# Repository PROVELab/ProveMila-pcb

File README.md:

View this project on [CADLAB.io](https://cadlab.io/project/27803). 

# ProveMila-pcb
Repository for KiCad files. Access through cadlab.io to view schematic and PCB

## Contents
* describe the different projects and files in this repo

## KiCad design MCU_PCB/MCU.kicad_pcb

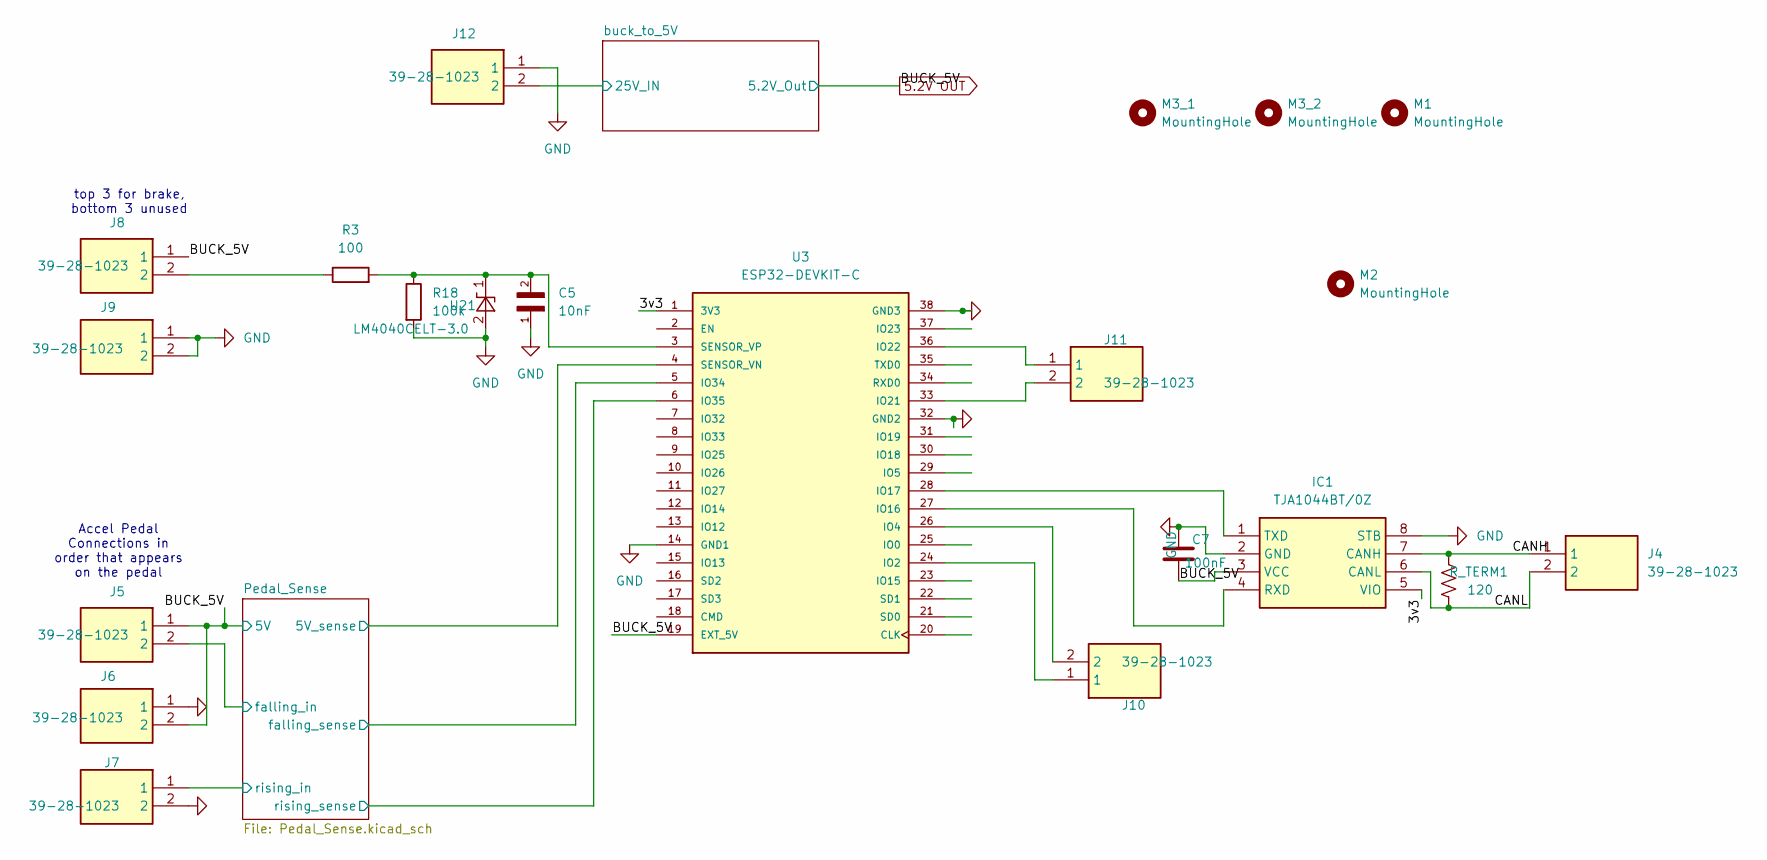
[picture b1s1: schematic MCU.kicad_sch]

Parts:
C5: 10nF; C_0805_2012Metric_Pad1.18x1.45mm_HandSolder
C7: 100nF; C_0805_2012Metric_Pad1.18x1.45mm_HandSolder; MPN 1206B104K500CT
IC1: TJA1044BT/0Z; SOIC127P600X175-8N; Mouser Part Number 771-TJA1044BT/0Z
J4, J5, J6, J7, J8, J9, J10, J11, J12: 39-28-1023; Mouser Part Number 538-39-28-1023
M1, M2, M3_1, M3_2: MountingHole; MountingHole_3.2mm_M3
R3: 100; R_0805_2012Metric_Pad1.20x1.40mm_HandSolder
R18: 100k; R_0805_2012Metric_Pad1.20x1.40mm_HandSolder
R_TERM1: 120; R_0805_2012Metric_Pad1.20x1.40mm_HandSolder; MPN RMCF1206JT120R
U3: ESP32-DEVKIT-C; MODULE_ESP32-DEVKITC; PARTREV N/A
U21: LM4040CELT-3.0; SOT-23

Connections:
5.2V OUT: C7.1, IC1.3 (VCC), J5.1, J6.2, J8.1, U3.19 (EXT_5V); also elsewhere on the board
/3v3: IC1.5 (VIO), U3.1 (3V3)
/CANH: IC1.7 (CANH), J4.1, R_TERM1.1
/CANL: IC1.6 (CANL), J4.2, R_TERM1.2
/Pedal_Sense/5V_sense: U3.4 (SENSOR_VN); also elsewhere on the board
/Pedal_Sense/falling_in: J5.2; also elsewhere on the board
/Pedal_Sense/falling_sense: U3.5 (IO34); also elsewhere on the board
/Pedal_Sense/rising_in: J7.1; also elsewhere on the board
/Pedal_Sense/rising_sense: U3.6 (IO35); also elsewhere on the board
/buck_to_5V/25V_IN: J12.2; also elsewhere on the board
GND: C5.1, C7.2, IC1.2 (GND), IC1.8 (STB), J6.1, J7.2, J9.1, J9.2, J12.1, R18.2, U3.14 (GND1), U3.32 (GND2), U3.38 (GND3), U21.2 (A); also elsewhere on the board
unnamed: IC1.4 (RXD), U3.27 (IO16)
unnamed: IC1.1 (TXD), U3.28 (IO17)
unnamed: J8.2, R3.1
unnamed: J10.1, U3.24 (IO2)
unnamed: J10.2, U3.26 (IO4)
unnamed: J11.2, U3.33 (IO21)
unnamed: J11.1, U3.36 (IO22)
unnamed: C5.2, R3.2, R18.1, U3.3 (SENSOR_VP), U21.1 (K)

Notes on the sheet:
Accel Pedal Connections in order that appears on the pedal
top 3 for brake, bottom 3 unused

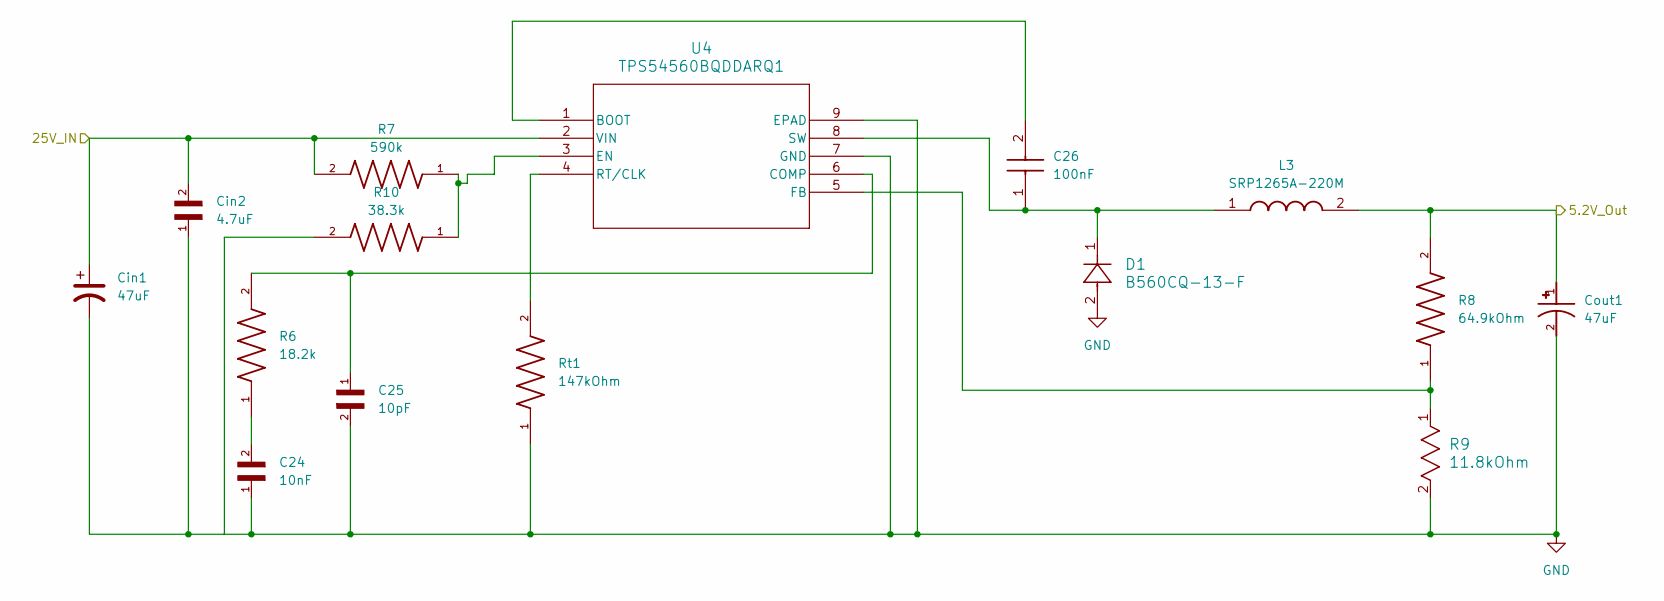
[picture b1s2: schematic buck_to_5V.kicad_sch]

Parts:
C24: 10nF; C_0805_2012Metric_Pad1.18x1.45mm_HandSolder
C25: 10pF; C_0805_2012Metric_Pad1.18x1.45mm_HandSolder
C26: 100nF; C_0805_2012Metric_Pad1.18x1.45mm_HandSolder
Cin1: 47uF; CP_Elec_6.3x7.7
Cin2: 4.7uF; C_1210_3225Metric_Pad1.33x2.70mm_HandSolder
Cout1: 47uF; CP_EIA-3528-21_Kemet-B_HandSolder
D1: B560CQ-13-F; D_SMC
L3: SRP1265A-220M; SRP1265A; Mouser Part Number 652-SRP1265A-220M
R6: 18.2k; R_0805_2012Metric_Pad1.20x1.40mm_HandSolder
R7: 590k; R_0805_2012Metric_Pad1.20x1.40mm_HandSolder
R8: 64.9kOhm; R_0805_2012Metric_Pad1.20x1.40mm_HandSolder
R9: 11.8kOhm; R_0805_2012Metric_Pad1.20x1.40mm_HandSolder
R10: 38.3k; R_0805_2012Metric_Pad1.20x1.40mm_HandSolder
Rt1: 147kOhm; R_0805_2012Metric_Pad1.20x1.40mm_HandSolder
U4: TPS54560BQDDARQ1; SOIC-8-1EP_3.9x4.9mm_P1.27mm_EP2.29x3mm

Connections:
5.2V OUT: Cout1.1, L3.2, R8.2; also elsewhere on the board
/buck_to_5V/25V_IN: Cin1.1, Cin2.2, R7.2, U4.2 (VIN); also elsewhere on the board
GND: C24.1, C25.2, Cin1.2, Cin2.1, Cout1.2, D1.2, R9.2, R10.2, Rt1.1, U4.7 (GND), U4.9 (EPAD); also elsewhere on the board
unnamed: C24.2, R6.1
unnamed: C26.2, U4.1 (BOOT)
unnamed: C25.1, R6.2, U4.6 (COMP)
unnamed: R7.1, R10.1, U4.3 (EN)
unnamed: R8.1, R9.1, U4.5 (FB)
unnamed: Rt1.2, U4.4 (RT/CLK)
unnamed: C26.1, D1.1, L3.1, U4.8 (SW)

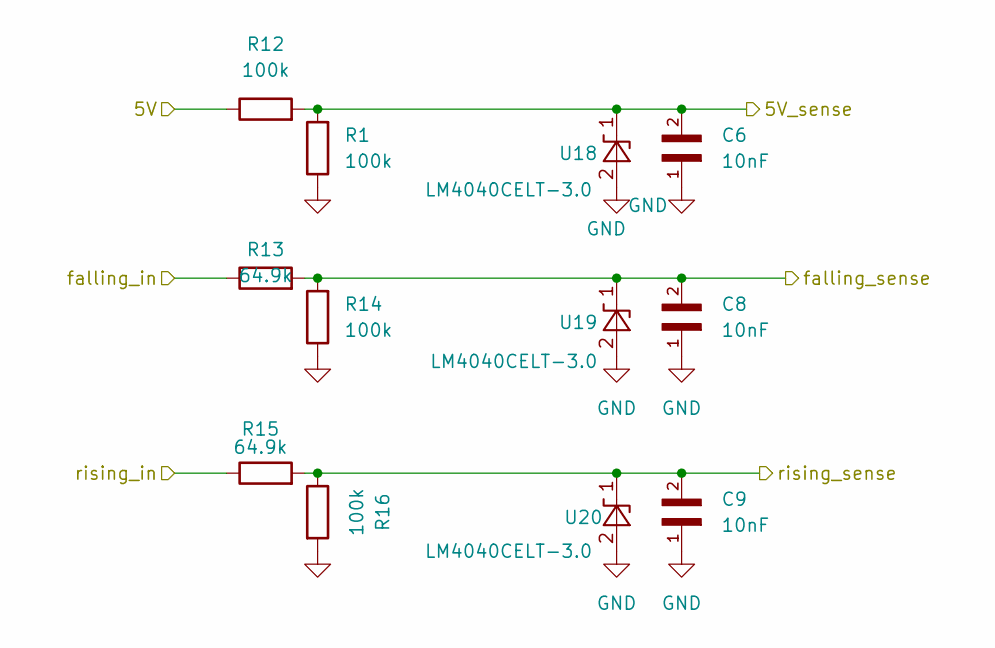
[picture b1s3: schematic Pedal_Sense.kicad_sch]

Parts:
C6, C8, C9: 10nF; C_0805_2012Metric_Pad1.18x1.45mm_HandSolder
R1, R12, R14, R16: 100k; R_0805_2012Metric_Pad1.20x1.40mm_HandSolder
R13, R15: 64.9k; R_0805_2012Metric_Pad1.20x1.40mm_HandSolder
U18, U19, U20: LM4040CELT-3.0; SOT-23

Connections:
5.2V OUT: R12.1; also elsewhere on the board
/Pedal_Sense/5V_sense: C6.2, R1.2, R12.2, U18.1 (K); also elsewhere on the board
/Pedal_Sense/falling_in: R13.1; also elsewhere on the board
/Pedal_Sense/falling_sense: C8.2, R13.2, R14.2, U19.1 (K); also elsewhere on the board
/Pedal_Sense/rising_in: R15.1; also elsewhere on the board
/Pedal_Sense/rising_sense: C9.2, R15.2, R16.1, U20.1 (K); also elsewhere on the board
GND: C6.1, C8.1, C9.1, R1.1, R14.1, R16.2, U18.2 (A), U19.2 (A), U20.2 (A); also elsewhere on the board

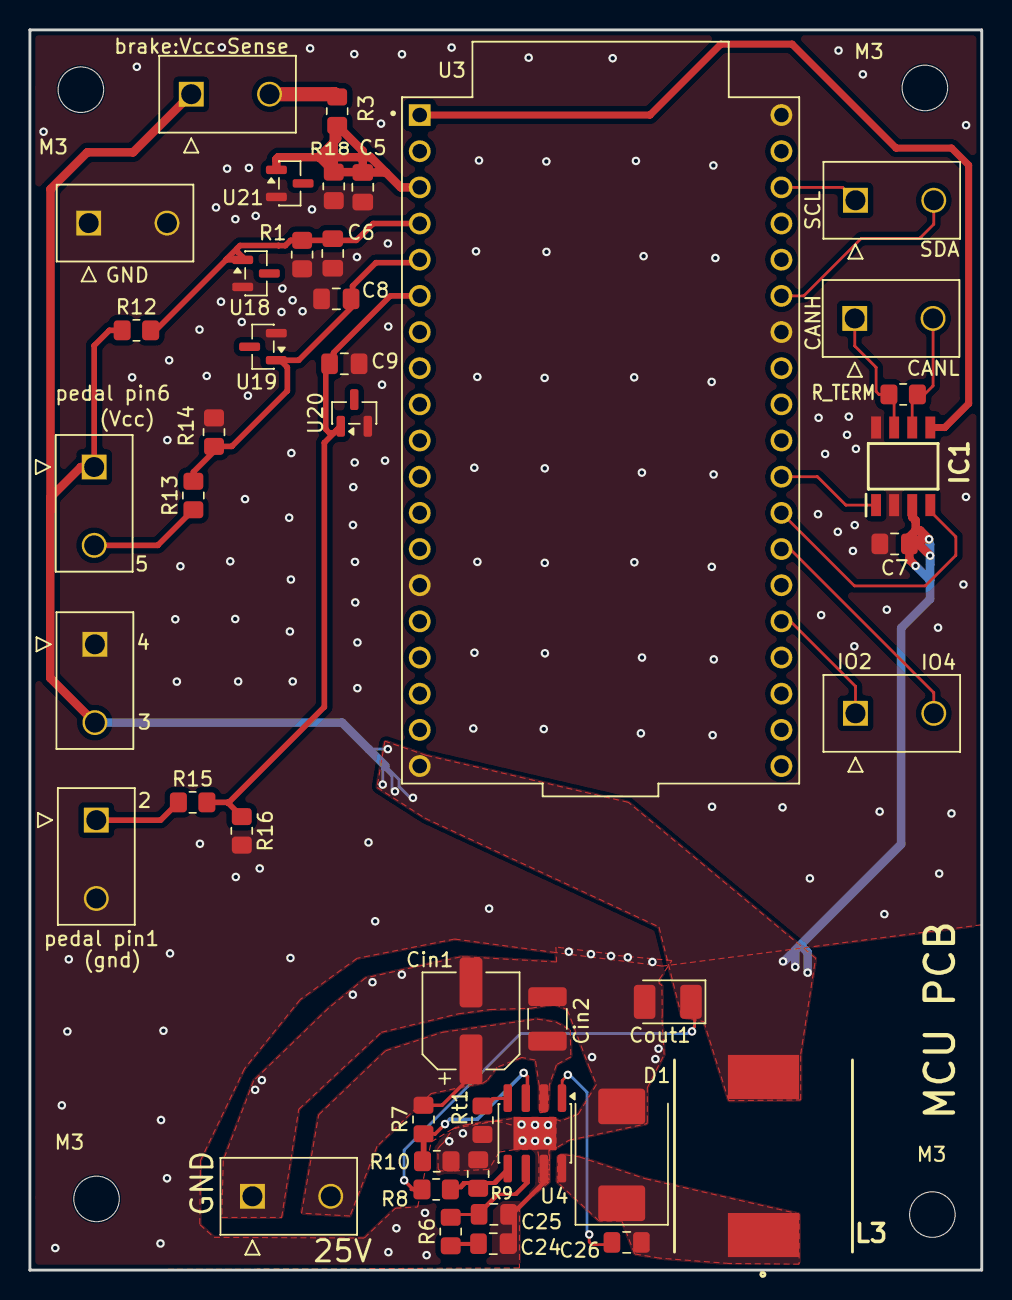
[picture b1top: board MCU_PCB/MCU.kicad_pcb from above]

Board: 2 copper layers, 66.8 x 87.1 mm, 48 parts (0 on the bottom side), 26 nets.

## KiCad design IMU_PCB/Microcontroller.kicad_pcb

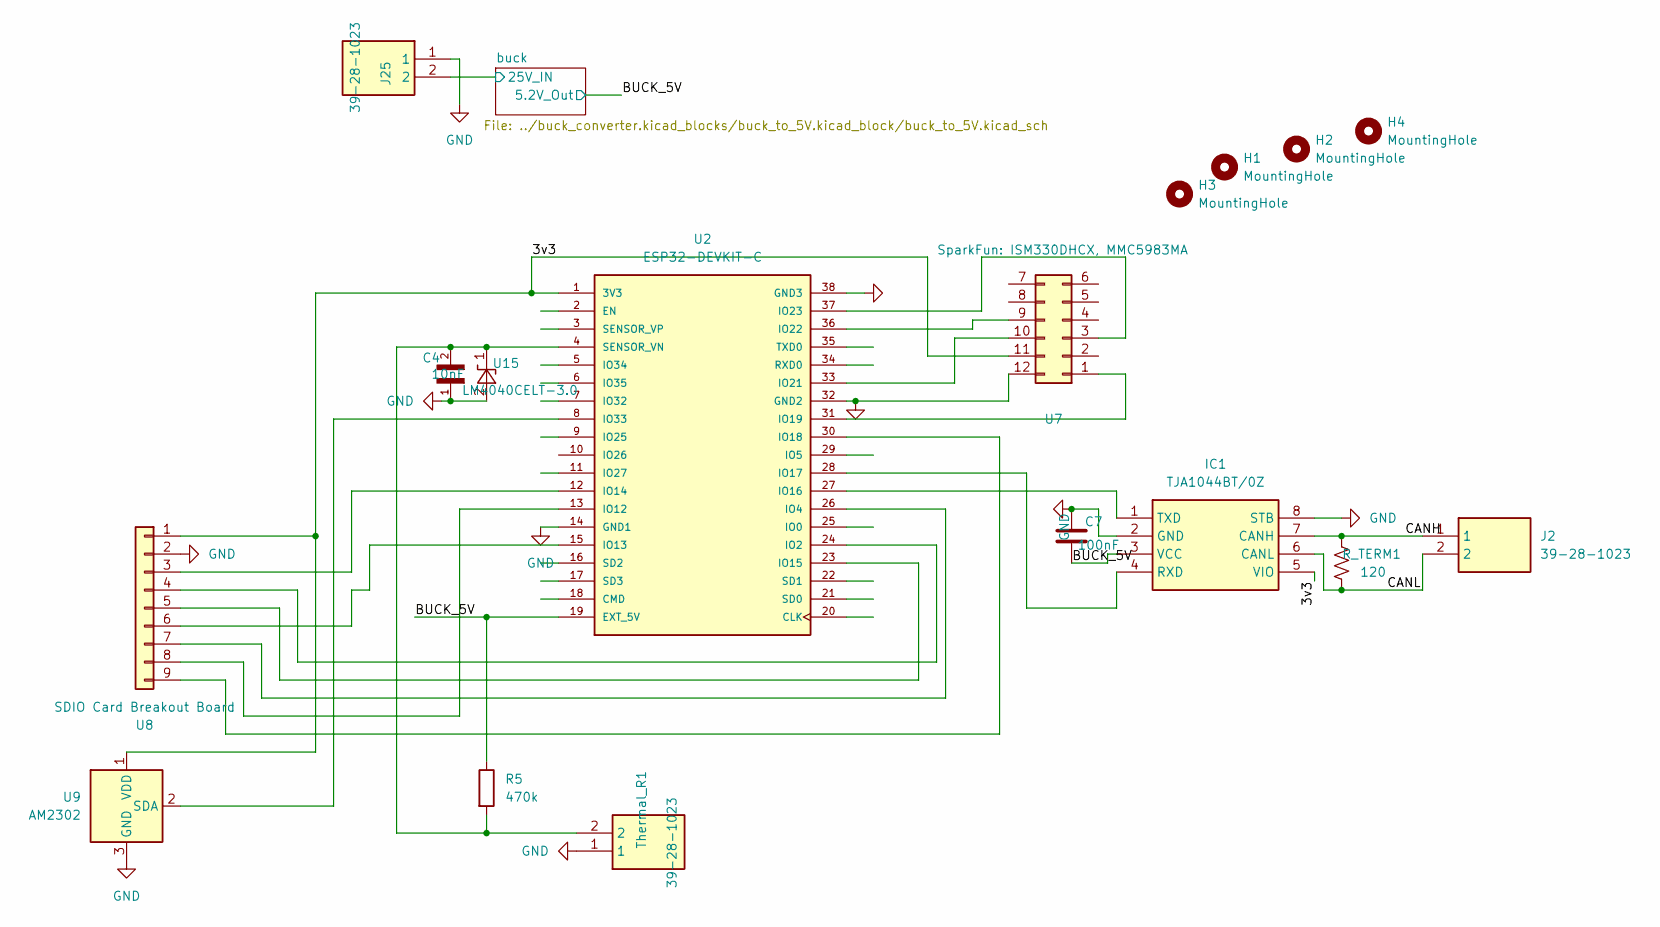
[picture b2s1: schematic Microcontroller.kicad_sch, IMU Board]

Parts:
C4: 10nF; C_0805_2012Metric_Pad1.18x1.45mm_HandSolder
C7: 100nF; C_0805_2012Metric_Pad1.18x1.45mm_HandSolder; MPN 1206B104K500CT
H1, H2, H3, H4: MountingHole; MountingHole_3.2mm_M3
IC1: TJA1044BT/0Z; SOIC127P600X175-8N; Mouser Part Number 771-TJA1044BT/0Z
J2, J25: 39-28-1023; Mouser Part Number 538-39-28-1023
R5: 470k; R_0805_2012Metric
R_TERM1: 120; R_0805_2012Metric_Pad1.20x1.40mm_HandSolder; MPN RMCF1206JT120R
Thermal_R1: 39-28-1023; Mouser Part Number 538-39-28-1023
U2: ESP32-DEVKIT-C; MODULE_ESP32-DEVKITC; PARTREV N/A
U7: SparkFun: ISM330DHCX, MMC5983MA; SparkFun 9DoF IMU Breakout - ISM330DHCX, MMC5983MA (Qwiic)
U8: SDIO Card Breakout Board; Adafruit SDIO card breakout
U9: AM2302; ASAIR_AM2302_P2.54mm_Vertical
U15: LM4040CELT-3.0; SOT-23

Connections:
/3v3: IC1.5 (VIO), U2.1 (3V3), U7.11, U8.1, U9.1 (VDD)
/BUCK_5V: C7.1, IC1.3 (VCC), R5.1, U2.19 (EXT_5V); also elsewhere on the board
/CANH: IC1.7 (CANH), J2.1, R_TERM1.1
/CANL: IC1.6 (CANL), J2.2, R_TERM1.2
/buck/25V_IN: J25.2; also elsewhere on the board
GND: C4.1, C7.2, IC1.2 (GND), IC1.8 (STB), J25.1, Thermal_R1.1, U2.14 (GND1), U2.32 (GND2), U2.38 (GND3), U7.12, U8.2, U9.3 (GND), U9.4 (GND), U15.2 (A); also elsewhere on the board
unnamed: IC1.4 (RXD), U2.28 (IO17)
unnamed: IC1.1 (TXD), U2.27 (IO16)
unnamed: U2.24 (IO2), U8.4
unnamed: U2.26 (IO4), U8.7
unnamed: U2.13 (IO12), U8.8
unnamed: U2.15 (IO13), U8.6
unnamed: U2.12 (IO14), U8.3
unnamed: U2.23 (IO15), U8.5
unnamed: U2.30 (IO18), U8.9
unnamed: U2.31 (IO19), U7.1
unnamed: U2.33 (IO21), U7.10
unnamed: U2.36 (IO22), U7.9
unnamed: U2.37 (IO23), U7.3
unnamed: U2.8 (IO33), U9.2 (SDA)
unnamed: C4.2, R5.2, Thermal_R1.2, U2.4 (SENSOR_VN), U15.1 (K)

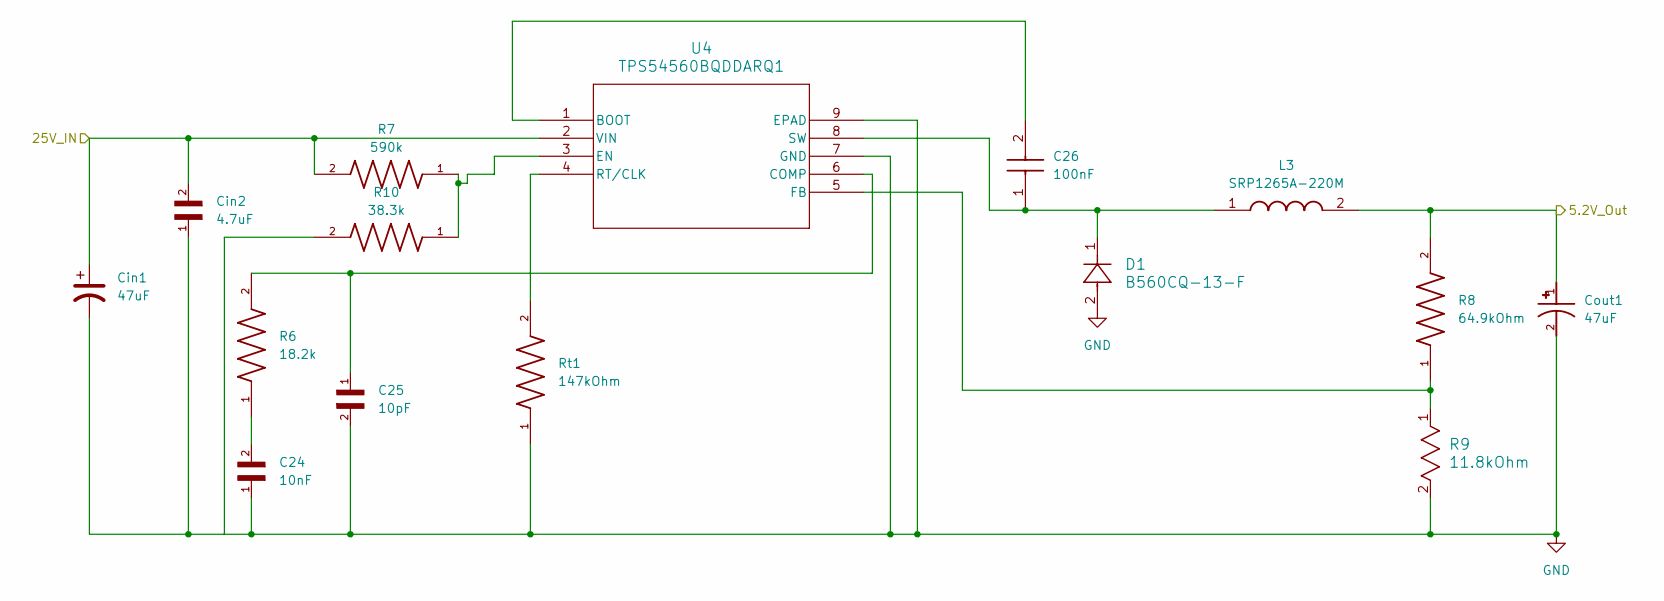
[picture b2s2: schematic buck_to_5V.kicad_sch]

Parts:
C24: 10nF; C_0805_2012Metric_Pad1.18x1.45mm_HandSolder
C25: 10pF; C_0805_2012Metric_Pad1.18x1.45mm_HandSolder
C26: 100nF; C_0805_2012Metric_Pad1.18x1.45mm_HandSolder
Cin1: 47uF; CP_Elec_6.3x7.7
Cin2: 4.7uF; C_1210_3225Metric_Pad1.33x2.70mm_HandSolder
Cout1: 47uF; CP_EIA-3528-21_Kemet-B_HandSolder
D1: B560CQ-13-F; D_SMC
L3: SRP1265A-220M; SRP1265A; Mouser Part Number 652-SRP1265A-220M
R6: 18.2k; R_0805_2012Metric_Pad1.20x1.40mm_HandSolder
R7: 590k; R_0805_2012Metric_Pad1.20x1.40mm_HandSolder
R8: 64.9kOhm; R_0805_2012Metric_Pad1.20x1.40mm_HandSolder
R9: 11.8kOhm; R_0805_2012Metric_Pad1.20x1.40mm_HandSolder
R10: 38.3k; R_0805_2012Metric_Pad1.20x1.40mm_HandSolder
Rt1: 147kOhm; R_0805_2012Metric_Pad1.20x1.40mm_HandSolder
U4: TPS54560BQDDARQ1; SOIC-8-1EP_3.9x4.9mm_P1.27mm_EP2.29x3mm

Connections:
/BUCK_5V: Cout1.1, L3.2, R8.2; also elsewhere on the board
/buck/25V_IN: Cin1.1, Cin2.2, R7.2, U4.2 (VIN); also elsewhere on the board
GND: C24.1, C25.2, Cin1.2, Cin2.1, Cout1.2, D1.2, R9.2, R10.2, Rt1.1, U4.7 (GND), U4.9 (EPAD); also elsewhere on the board
unnamed: C24.2, R6.1
unnamed: C26.2, U4.1 (BOOT)
unnamed: C25.1, R6.2, U4.6 (COMP)
unnamed: R7.1, R10.1, U4.3 (EN)
unnamed: R8.1, R9.1, U4.5 (FB)
unnamed: Rt1.2, U4.4 (RT/CLK)
unnamed: C26.1, D1.1, L3.1, U4.8 (SW)

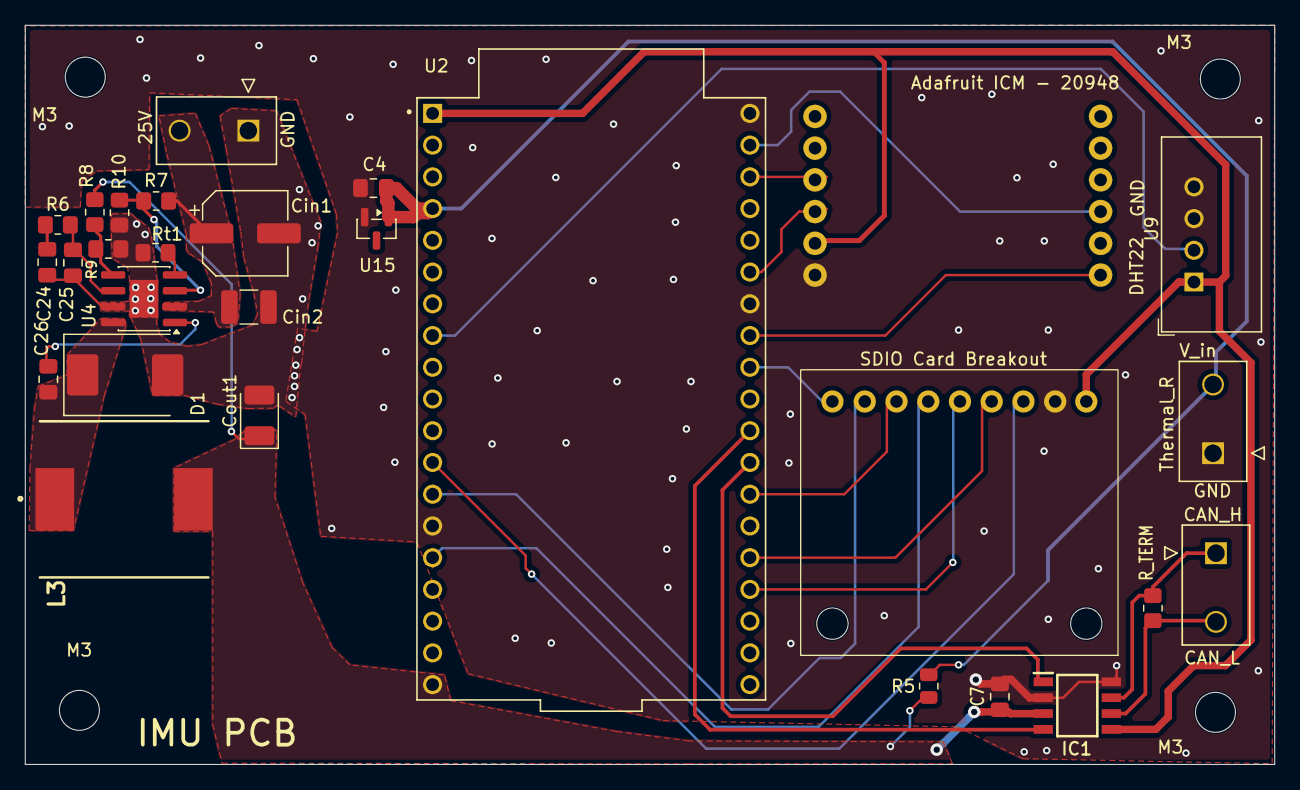
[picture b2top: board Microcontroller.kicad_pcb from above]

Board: 2 copper layers, 100.0 x 59.2 mm, 32 parts (1 on the bottom side), 28 nets.

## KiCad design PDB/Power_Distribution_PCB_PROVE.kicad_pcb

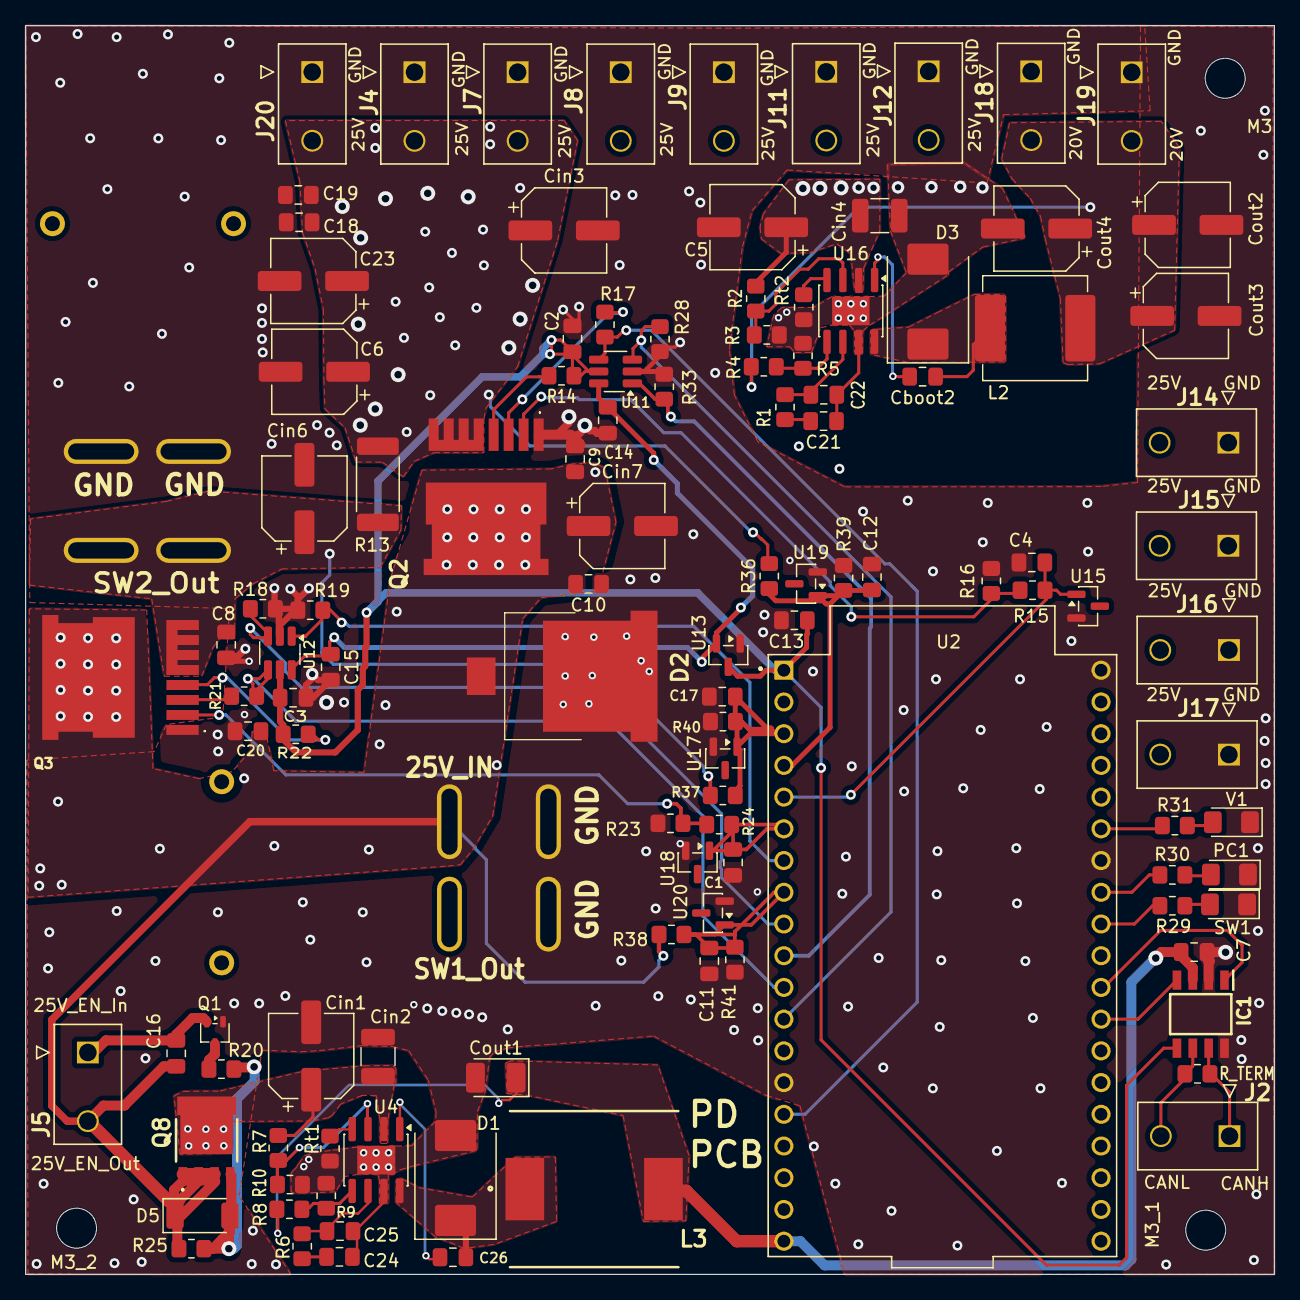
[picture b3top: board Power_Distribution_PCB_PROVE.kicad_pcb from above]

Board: 4 copper layers, 100.0 x 100.0 mm, 119 parts (0 on the bottom side), 53 nets.

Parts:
C1, C4, C11, C12, C17, C24: 10nF; C_0805_2012Metric_Pad1.18x1.45mm_HandSolder
C2, C3, C7, C8, C9, C10, C13, C14, C15, C16, C18, C19, C20, C26: 100nF; C_0805_2012Metric_Pad1.18x1.45mm_HandSolder
C5, C6, C23: 47uF; CP_Elec_6.3x7.7
C21: 3.9nF; C_0805_2012Metric_Pad1.18x1.45mm_HandSolder
C22: 330pF; C_0805_2012Metric_Pad1.18x1.45mm_HandSolder
C25: 10pF; C_0805_2012Metric_Pad1.18x1.45mm_HandSolder
Cboot2: 100nF; C_0805_2012Metric_Pad1.18x1.45mm_HandSolder
Cin1, Cin3, Cin6, Cin7: 47uF; CP_Elec_6.3x7.7
Cin2, Cin4: 4.7uF; C_1210_3225Metric_Pad1.33x2.70mm_HandSolder
Cout1: 47uF; CP_EIA-3528-21_Kemet-B_HandSolder
Cout2, Cout3, Cout4: 47uF; CP_Elec_6.3x7.7
D1, D3: B560CQ-13-F; D_SMC
D2: SLD8S30A
D5: PDZVTR10B; D_SOD-128
IC1: TJA1044BT/0Z; SOIC127P600X175-8N
J1, J3: Conn_02x02_Top_Bottom; Anderson_PP1545_45A_2b2
J2, J4, J5, J7, J8, J9, J11, J12, J14, J15, J16, J17, J18, J19, J20: 39-28-1023
L2: 8.2uH; L_Vishay_IHLP-3232
L3: SRP1265A-220M; SRP1265A
M3, M3_1, M3_2: MountingHole; MountingHole_3.2mm_M3
PC1: SML-S13UTT68; LED_1206_3216Metric_Pad1.42x1.75mm_HandSolder
Q1: DTC144EU3HZGT106; SOT-323_SC-70
Q2, Q3: BTH500151LUAAUMA1; BTS500101LUA
Q8: BUK6Y55-80PX
R1: 36.5k; R_0805_2012Metric_Pad1.20x1.40mm_HandSolder
R2, R7: 590k; R_0805_2012Metric_Pad1.20x1.40mm_HandSolder
R3, R10: 38.3k; R_0805_2012Metric_Pad1.20x1.40mm_HandSolder
R4: 271kOhm; R_0805_2012Metric_Pad1.20x1.40mm_HandSolder
R5: 11.3kOhm; R_0805_2012Metric_Pad1.20x1.40mm_HandSolder
R6, R18, R19, R20, R28, R33: 18.2k; R_0805_2012Metric_Pad1.20x1.40mm_HandSolder
R8: 64.9kOhm; R_0805_2012Metric_Pad1.20x1.40mm_HandSolder
R9: 11.8kOhm; R_0805_2012Metric_Pad1.20x1.40mm_HandSolder
R13: 470; R_2512_6332Metric_Pad1.40x3.35mm_HandSolder
R14, R15, R17, R21, R22, R24: 4.7k; R_0805_2012Metric_Pad1.20x1.40mm_HandSolder
R16, R23: 2k; R_0805_2012Metric_Pad1.20x1.40mm_HandSolder
R25, R39, R40, R41: 100k; R_0805_2012Metric_Pad1.20x1.40mm_HandSolder
R29, R30, R31: 270; R_0805_2012Metric_Pad1.20x1.40mm_HandSolder
R36, R37, R38: 1M; R_0805_2012Metric_Pad1.20x1.40mm_HandSolder
R_TERM1: 120; R_0805_2012Metric_Pad1.20x1.40mm_HandSolder
Rt1: 147kOhm; R_0805_2012Metric_Pad1.20x1.40mm_HandSolder
Rt2: 133kOhm; R_0805_2012Metric_Pad1.20x1.40mm_HandSolder
SW1: SML-S13UTT68; LED_1206_3216Metric_Pad1.42x1.75mm_HandSolder
U2: ESP32-DEVKIT-C; MODULE_ESP32-DEVKITC
U4, U16: TPS54560BQDDARQ1; SOIC-8-1EP_3.9x4.9mm_P1.27mm_EP2.29x3mm
U11, U12: 74LVC1G175; SOT-23-6_Handsoldering
U13: TLV809EA29DBZR; SOT-23
U15, U17, U18, U19, U20: LM4040CELT-3.0; SOT-23
V1: SML-S13UTT68; LED_1206_3216Metric_Pad1.42x1.75mm_HandSolder

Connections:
/3v3: C2.2, C3.2, C13.1, IC1.5 (VIO), R14.1, R22.1, U2.1 (3V3), U11.5 (VCC), U12.5 (VCC), U13.3 (V_{DD})
/25V_In: C9.2, C10.2, C16.1, C20.2, Cin7.1, D2.1 (K), D5.1 (K), J1.1, J5.2, Q2.9 (VS_1), Q2.10 (VS_2), Q2.11 (VS_3), Q3.9 (VS_1), Q3.10 (VS_2), Q3.11 (VS_3), Q8.1 (S_1), Q8.2 (S_2), Q8.3 (S_3), R25.1, R38.2
/BUCK_5V: C7.1, Cout1.1, IC1.3 (VCC), L3.2, R8.2, U2.19 (EXT_5V)
/CANH: IC1.7 (CANH), J2.1, R_TERM1.1
/CANL: IC1.6 (CANL), J2.2, R_TERM1.2
/Driver_LV_Enable_Switch/25V_User_Switched: Cin1.1, Cin2.2, Q8.5 (D_1), Q8.6 (D_2), R7.2, U4.2 (VIN)
/Inverter_20V: Cout2.1, Cout3.1, Cout4.1, J18.2, J19.2, L2.1, R4.2
/PC_Err: PC1.2 (A), R30.2
/SW1_25V: C5.1, C6.1, C18.1, C19.1, C23.1, Cin3.1, Cin4.2, J1.2, J4.2, J7.2, J8.2, J9.2, J11.2, J12.2, J14.2, J15.2, J16.2, J17.2, J20.2, Q2.5 (OUT_1), Q2.6 (OUT_2), Q2.7 (OUT_3), Q2.8 (OUT_4), Q2.12 (OUT_5), R2.2, R13.2, R36.2, U16.2 (VIN)
/SW2_25V: C8.1, Cin6.1, J3.3, J3.4, Q3.5 (OUT_1), Q3.6 (OUT_2), Q3.7 (OUT_3), Q3.8 (OUT_4), Q3.12 (OUT_5), R13.1, R37.2
/SW_Err: R29.2, SW1.2 (A)
/Switch/Switch_1_CLK: R33.2, U2.10 (IO26), U11.1 (C)
/Switch/Switch_1_Data: R28.2, U2.12 (IO14), U11.3 (D)
/Switch/Switch_1_IS: C4.2, R15.2, U2.5 (IO34), U15.1 (K)
/Switch/Switch_1_State_FB: R17.1, U2.15 (IO13), U11.4 (Q)
/Switch/Switch_2_CLK: R19.2, U2.7 (IO32), U12.1 (C)
/Switch/Switch_2_Data: R18.2, U2.9 (IO25), U12.3 (D)
/Switch/Switch_2_IS: C1.2, R24.2, U2.6 (IO35), U18.1 (K)
/Switch/Switch_2_State_FB: R21.1, U2.11 (IO27), U12.4 (Q)
/V_Err: R31.2, V1.2 (A)
/V_Sense_Div/SW1_Sense: C12.2, R36.1, R39.2, U2.4 (SENSOR_VN), U19.1 (K)
/V_Sense_Div/SW2_Sense: C17.2, R37.1, R40.2, U2.3 (SENSOR_VP), U17.1 (K)
/V_Sense_Div/V_Bat_Sense: C11.2, R38.1, R41.1, U2.8 (IO33), U20.1 (K)
GND: C1.1, C2.1, C3.1, C4.1, C5.2, C6.2, C7.2, C8.2, C9.1, C10.1, C11.1, C12.1, C13.2, C14.2, C15.2, C17.1, C18.2, C19.2, C20.1, C21.1, C22.2, C23.2, C24.1, C25.2, Cin1.2, Cin2.1, Cin3.2, Cin4.1, Cin6.2, Cin7.2, Cout1.2, Cout2.2, Cout3.2, Cout4.2, D1.2, D2.2 (A_1), D2.3 (A_2), D3.2, IC1.2 (GND), IC1.8 (STB), J1.3, J1.4, J3.1, J3.2, J4.1, J7.1, J8.1, J9.1, J11.1, J12.1, J14.1, J15.1, J16.1, J17.1, J18.1, J19.1, J20.1, PC1.1 (K), Q1.1 (E), Q2.1 (GND), Q3.1 (GND), R3.2, R5.2, R9.2, R10.2, R16.1, R18.1, R19.1, R23.1, R28.1, R33.1, R39.1, R40.1, R41.2, Rt1.1, Rt2.1, SW1.1 (K), U2.14 (GND1), U2.32 (GND2), U2.38 (GND3), U4.7 (GND), U4.9 (EPAD), U11.2 (GND), U12.2 (GND), U13.1 (GND), U15.2 (A), U16.7 (GND), U16.9 (EPAD), U17.2 (A), U18.2 (A), U19.2 (A), U20.2 (A), V1.1 (K)
unnamed: C21.2, R1.1
unnamed: C24.2, R6.1
unnamed: D5.2 (A), Q8.4 (G), R20.1, R25.2
unnamed: IC1.4 (RXD), U2.27 (IO16)
unnamed: IC1.1 (TXD), U2.28 (IO17)
unnamed: C16.2, J5.1, Q1.2 (B)
unnamed: Q1.3 (C), R20.2
unnamed: Q2.4 (DEN), R14.2
unnamed: Q2.3 (IN), R17.2
unnamed: Q2.2 (IS), R15.1, R16.2
unnamed: Q3.4 (DEN), R22.2
unnamed: Q3.3 (IN), R21.2
unnamed: Q3.2 (IS), R23.2, R24.1
unnamed: R29.1, U2.30 (IO18)
unnamed: R30.1, U2.31 (IO19)
unnamed: R31.1, U2.33 (IO21)
unnamed: C26.2, U4.1 (BOOT)
unnamed: C25.1, R6.2, U4.6 (COMP)
unnamed: R7.1, R10.1, U4.3 (EN)
unnamed: R8.1, R9.1, U4.5 (FB)
unnamed: Rt1.2, U4.4 (RT/CLK)
unnamed: C26.1, D1.1, L3.1, U4.8 (SW)
unnamed: C14.1, C15.1, U11.6 (~CLR), U12.6 (~CLR), U13.2 (RESET)
unnamed: Cboot2.2, U16.1 (BOOT)
unnamed: C22.1, R1.2, U16.6 (COMP)
unnamed: R2.1, R3.1, U16.3 (EN)
unnamed: R4.1, R5.1, U16.5 (FB)
unnamed: Rt2.2, U16.4 (RT/CLK)
unnamed: Cboot2.1, D3.1, L2.2, U16.8 (SW)

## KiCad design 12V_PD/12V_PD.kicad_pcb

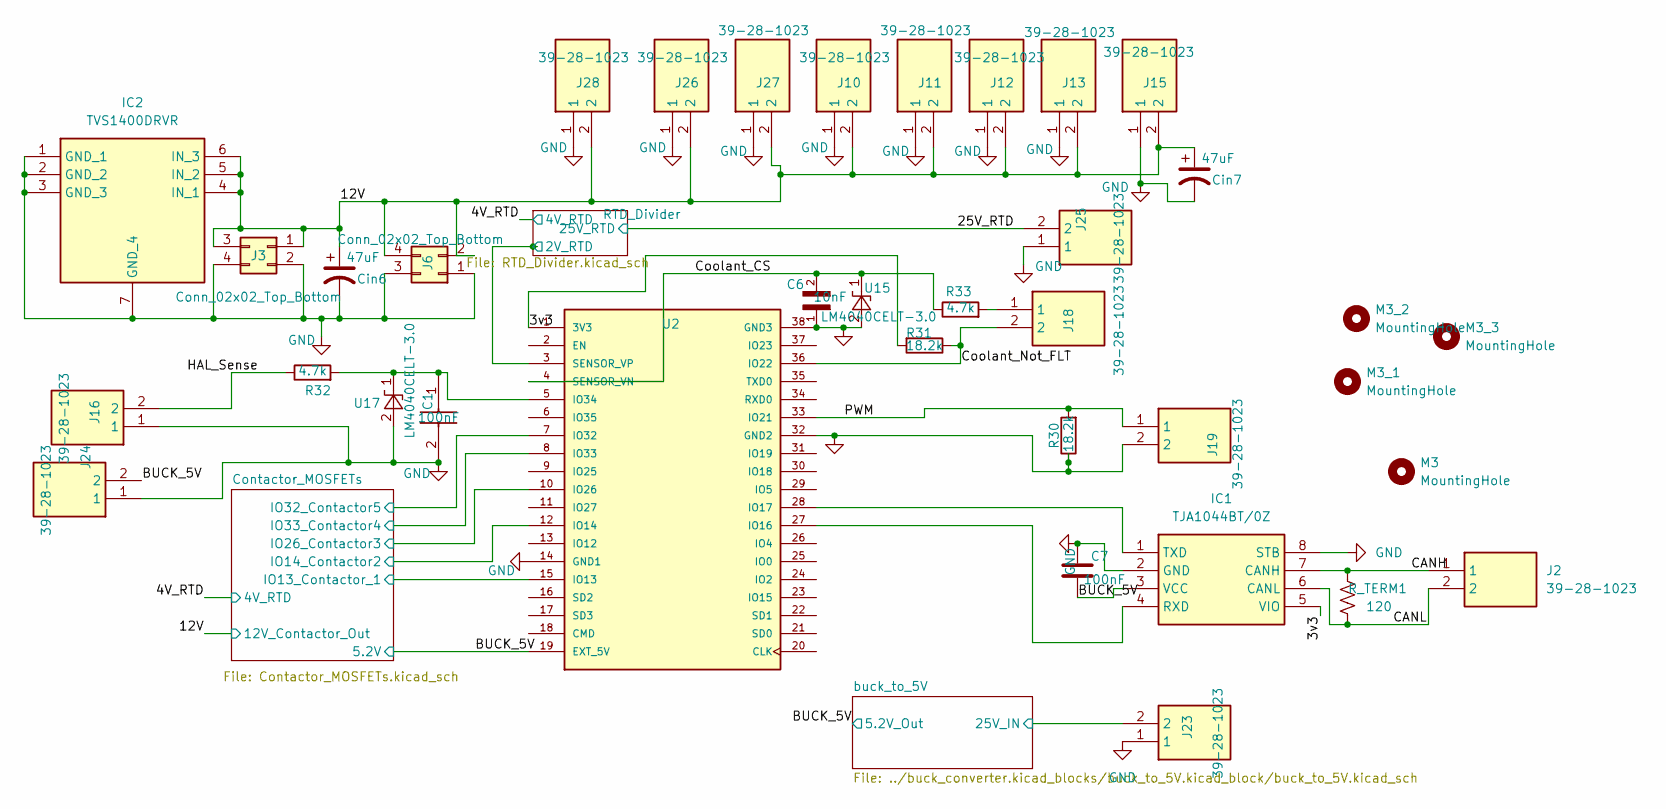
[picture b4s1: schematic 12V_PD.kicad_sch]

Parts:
C1: 100nF; C_0805_2012Metric_Pad1.18x1.45mm_HandSolder
C6: 10nF; C_0805_2012Metric_Pad1.18x1.45mm_HandSolder
C7: 100nF; C_0805_2012Metric_Pad1.18x1.45mm_HandSolder; MPN 1206B104K500CT
Cin6, Cin7: 47uF; CP_Elec_6.3x7.7
IC1: TJA1044BT/0Z; SOIC127P600X175-8N; Mouser Part Number 771-TJA1044BT/0Z
IC2: TVS1400DRVR; SON65P200X200X80-7N; Mouser Part Number 595-TVS1400DRVR
J2, J10, J11, J12, J13, J15, J16, J18, J19, J23, J24, J25, J26, J27, J28: 39-28-1023; Mouser Part Number 538-39-28-1023
J3, J6: Conn_02x02_Top_Bottom; Anderson_PP1545_45A_2b2
M3, M3_1, M3_2, M3_3: MountingHole; MountingHole_3.2mm_M3
R30, R31: 18.2k; R_0805_2012Metric_Pad1.20x1.40mm_HandSolder
R32, R33: 4.7k; R_0805_2012Metric_Pad1.20x1.40mm_HandSolder
R_TERM1: 120; R_0805_2012Metric_Pad1.20x1.40mm_HandSolder; MPN RMCF1206JT120R
U2: ESP32-DEVKIT-C; MODULE_ESP32-DEVKITC; PARTREV N/A
U15, U17: LM4040CELT-3.0; SOT-23

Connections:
/3v3: IC1.5 (VIO), R31.2, U2.1 (3V3)
/12V: Cin6.1, Cin7.1, IC2.4 (IN_1), IC2.5 (IN_2), IC2.6 (IN_3), J3.1, J3.3, J6.2, J6.4, J10.2, J11.2, J12.2, J13.2, J15.2, J26.2, J27.2, J28.2; also elsewhere on the board
/25V_RTD: J25.2; also elsewhere on the board
/BUCK_5V: C7.1, IC1.3 (VCC), J24.2, U2.19 (EXT_5V); also elsewhere on the board
/CANH: IC1.7 (CANH), J2.1, R_TERM1.1
/CANL: IC1.6 (CANL), J2.2, R_TERM1.2
/Contactor_MOSFETs/IO13_Contactor_1: U2.15 (IO13); also elsewhere on the board
/Contactor_MOSFETs/IO14_Contactor2: U2.12 (IO14); also elsewhere on the board
/Contactor_MOSFETs/IO26_Contactor3: U2.10 (IO26); also elsewhere on the board
/Contactor_MOSFETs/IO32_Contactor5: U2.7 (IO32); also elsewhere on the board
/Contactor_MOSFETs/IO33_Contactor4: U2.8 (IO33); also elsewhere on the board
/Coolant_CS: C6.2, R33.1, U2.4 (SENSOR_VN), U15.1 (K)
/Coolant_Not_FLT: J18.2, R31.1, U2.36 (IO22)
/HAL_Sense: J16.2, R32.1
/PWM: J19.1, R30.2, U2.33 (IO21)
/RTD_Divider/2V_RTD: U2.3 (SENSOR_VP); also elsewhere on the board
/buck_to_5V/25V_IN: J23.2; also elsewhere on the board
GND: C1.2, C6.1, C7.2, Cin6.2, Cin7.2, IC1.2 (GND), IC1.8 (STB), IC2.1 (GND_1), IC2.2 (GND_2), IC2.3 (GND_3), IC2.7 (GND_4), J3.2, J3.4, J6.1, J6.3, J10.1, J11.1, J12.1, J13.1, J15.1, J16.1, J19.2, J23.1, J24.1, J25.1, J26.1, J27.1, J28.1, R30.1, U2.14 (GND1), U2.32 (GND2), U2.38 (GND3), U15.2 (A), U17.2 (A); also elsewhere on the board
unnamed: IC1.4 (RXD), U2.27 (IO16)
unnamed: IC1.1 (TXD), U2.28 (IO17)
unnamed: J18.1, R33.2
unnamed: C1.1, R32.2, U2.5 (IO34), U17.1 (K)

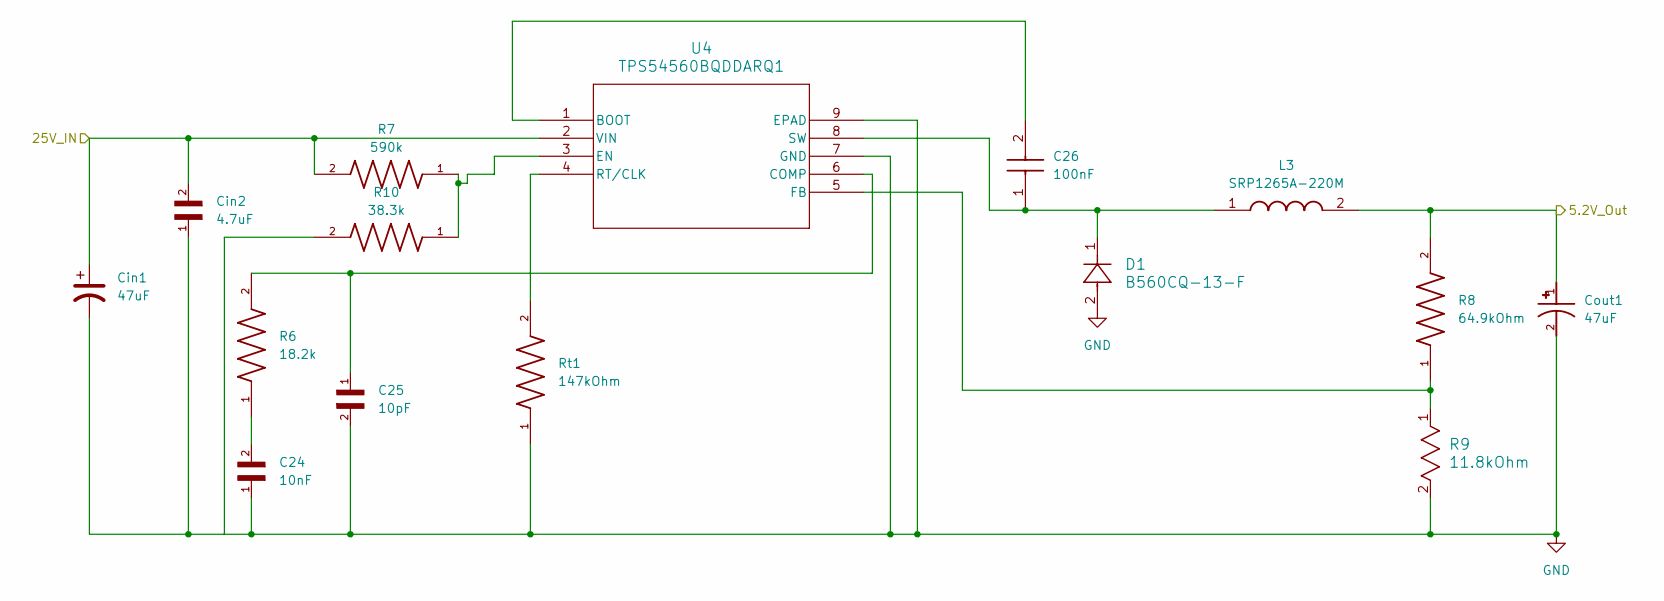
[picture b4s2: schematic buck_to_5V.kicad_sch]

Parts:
C24: 10nF; C_0805_2012Metric_Pad1.18x1.45mm_HandSolder
C25: 10pF; C_0805_2012Metric_Pad1.18x1.45mm_HandSolder
C26: 100nF; C_0805_2012Metric_Pad1.18x1.45mm_HandSolder
Cin1: 47uF; CP_Elec_6.3x7.7
Cin2: 4.7uF; C_1210_3225Metric_Pad1.33x2.70mm_HandSolder
Cout1: 47uF; CP_EIA-3528-21_Kemet-B_HandSolder
D1: B560CQ-13-F; D_SMC
L3: SRP1265A-220M; SRP1265A; Mouser Part Number 652-SRP1265A-220M
R6: 18.2k; R_0805_2012Metric_Pad1.20x1.40mm_HandSolder
R7: 590k; R_0805_2012Metric_Pad1.20x1.40mm_HandSolder
R8: 64.9kOhm; R_0805_2012Metric_Pad1.20x1.40mm_HandSolder
R9: 11.8kOhm; R_0805_2012Metric_Pad1.20x1.40mm_HandSolder
R10: 38.3k; R_0805_2012Metric_Pad1.20x1.40mm_HandSolder
Rt1: 147kOhm; R_0805_2012Metric_Pad1.20x1.40mm_HandSolder
U4: TPS54560BQDDARQ1; SOIC-8-1EP_3.9x4.9mm_P1.27mm_EP2.29x3mm

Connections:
/BUCK_5V: Cout1.1, L3.2, R8.2; also elsewhere on the board
/buck_to_5V/25V_IN: Cin1.1, Cin2.2, R7.2, U4.2 (VIN); also elsewhere on the board
GND: C24.1, C25.2, Cin1.2, Cin2.1, Cout1.2, D1.2, R9.2, R10.2, Rt1.1, U4.7 (GND), U4.9 (EPAD); also elsewhere on the board
unnamed: C24.2, R6.1
unnamed: C26.2, U4.1 (BOOT)
unnamed: C25.1, R6.2, U4.6 (COMP)
unnamed: R7.1, R10.1, U4.3 (EN)
unnamed: R8.1, R9.1, U4.5 (FB)
unnamed: Rt1.2, U4.4 (RT/CLK)
unnamed: C26.1, D1.1, L3.1, U4.8 (SW)
